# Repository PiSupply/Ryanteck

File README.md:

# Ryanteck

[Pi-Supply](https://uk.pi-supply.com) is one of the official distributors and manufacturers of [Ryanteck](https://ryanteck.uk) products including; RTK.GPIO, RTK Motor Controller board and RTK Traffic HAT for the Raspberry Pi. These product were designed by Ryan Walmsley at Ryanteck Ltd.

# Board overview

## RTK.GPIO

The RTK GPIO board allows you to connect the world of physical computing to you desktop PC or laptop. The RTK GPIO board emulates the original Raspberry Pi 28-pin GPIO header allowing you to program for the Raspberry Pi on your computer. The board is fully compatible with Windows, Mac OS and Linux and supports a range of programming languages such as Python.

The board connects to your computer using a micro USB cable , which also provides power to the board.

## RTK Motor Controller

The new and improved RTK-000-001-V3 / Motor Controller Board for Raspberry Pi is now pre-soldered and features a new and improved design breaking out the GPIO Pins to the side of the board.

The Ryanteck Raspberry Pi Motor Controller Board is a simple to use & budget friendly motor controller board for the Raspberry Pi which allows you to easily control 2 motors in both directions with some simple coding!

Once you receive the board, simply place it on the Raspberry Pi's GPIO header, screw in a power pack, add your motors and then start programming. We officially support Python at this point in time although you can use it with any language that allows you to control the GPIO pins including Scratch, C, Java, PHP, Bash, Node.JS etc.

## Traffic HAT

The Traffic HAT is designed for beginners to teach the basics or programming the real world with a traffic light sequence of LEDs. The HAT has 3 on-board LEDs (Red, Yellow, Green) with a push button and piezo buzzer.

The new Pi Supply branded Traffic HAT comes fully soldered and ready to go!

## Traffic pHAT

The Traffic pHAT is designed as a simple board to easily show the status of all the things! It is very much like the larger traffic HAT but with only 3 on-board LEDS (Red, Yellow, Green) and in a pHAT format. It comes with a 40 way GPIO header, so it perfect for any Raspberry Pi board with a 40 way connector.

The Traffic pHAT Comes fully assembled and ready to go!

## Where to buy

* [Pi Supply](https://uk.pi-supply.com)

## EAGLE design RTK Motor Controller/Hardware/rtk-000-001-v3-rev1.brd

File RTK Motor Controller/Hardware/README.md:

# RTK Motor Controller Board

The above image of the RTK Motor Controller Board PCB is used in the following descriptions to highlight some of the inputs and outputs and other useful hardware information of the board.

## Motor-1 Motor-2

These two screw terminals are used to connect two motors to the motor controller board. You can connect the wires from your motor to the terminals by un-screwing the screw and inserting the wire into the hole and the screw the terminal back down. The red wire should be inserted into the most left screw hole and the black next to it for a clockwise motor direction.

## VCC2

VCC2 screw terminal provides power to the motors and the motor controller chip. You can connect a power supply from 4.5V to 12V  with current up to 1A. The left terminal it the +V (Red wire) and the right terminal is GND (Black wire).

## GPIO Breakout Headers

There are two rows of 10 GPIO headers, which are breakout from the main 26-way Raspberry Pi GPIO header, JP2 and JP3 and also connected to the power input of VCC.

| JP3 | GPIO | JP2 | GPIO |
|-----|------|-----|------|
| 1   | VCC  | 1   | 5V      |
| 2   | 3V3  | 2   | 3V3     |
| 3   | GPIO 2| 3  | GPIO 14 |
| 4   | GPIO 3| 4  | GPIO 15 |
| 5   | GPIO 4| 5  | GPIO 24 |
| 6   | GPIO 10| 6 | GPIO 25 |
| 7   | GPIO 9| 7  | GPIO 8  |
| 8   | GPIO 11| 8 | GPIO 7  |
| 9   | GND | 9    | GND     |
| 10  | GND | 10   | GND     |

## SN75441ONE

The main active component is the SN75441ONE H-Bridge motor controller by TI.

| Pin Number | Label  | Connected to |
|------------|--------|--------------|
| 1          | 1,2 EN | VCC          |
| 2          | 1A     | GPIO 17      |
| 3          | 1Y     | Motor A 1    |
| 4          | GND_3  | GND          |
| 5          | GND_4  | GND          |
| 6          | 2Y     | Motor A 2    |
| 7          | 2A     | GPIO 18      |
| 8          | VCC2   | VCC/2        |
| 9          | 3,4 EN | VCC          |
| 10         | 3A     | GPIO 22      |
| 11         | 3Y     | Motor B 2    |
| 12         | GND    | GND          |
| 13         | GND_2  | GND          |
| 14         | 4Y     | Motor B 1    |
| 15         | 4A     | GPIO 23      |
| 16         | VCC 1  | VCC          |

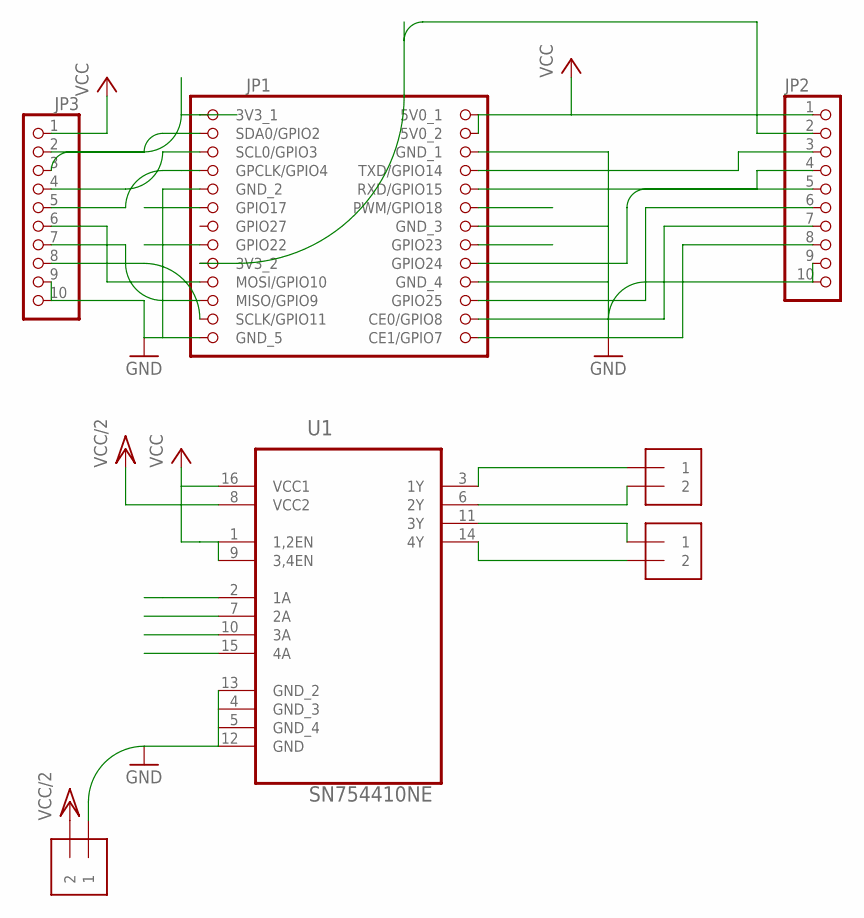
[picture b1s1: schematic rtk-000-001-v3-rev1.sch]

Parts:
JP1: RPIGPIOPINHD-2X13; 2X13
JP2, JP3: PINHD-1X10; 1X10
MOTOR-1, MOTOR-2: 1X2-3.5MM; 3.5MMTERM
U1: SN754410NE; DIP254P762X508-16
VCC2: 1X2-3.5MM; 3.5MMTERM

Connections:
17: JP1.11 (GPIO17), U1.2 (1A)
18: JP1.12 (PWM/GPIO18), U1.7 (2A)
22: JP1.15 (GPIO22), U1.10 (3A)
23: JP1.16 (GPIO23), U1.15 (4A)
GND: JP1.6 (GND_1), JP1.9 (GND_2), JP1.14 (GND_3), JP1.20 (GND_4), JP1.25 (GND_5), JP2.9, JP2.10, JP3.9, JP3.10, U1.4 (GND_3), U1.5 (GND_4), U1.12 (GND), U1.13 (GND_2), VCC2.1
GPIO24: JP1.18 (GPIO24), JP2.5
GPIO25: JP1.22 (GPIO25), JP2.6
unnamed: MOTOR-2.1, U1.11 (3Y)
unnamed: JP1.7 (GPCLK/GPIO4), JP3.5
unnamed: JP1.23 (SCLK/GPIO11), JP3.8
unnamed: MOTOR-2.2, U1.14 (4Y)
unnamed: MOTOR-1.2, U1.6 (2Y)
unnamed: MOTOR-1.1, U1.3 (1Y)
unnamed: JP1.19 (MOSI/GPIO10), JP3.6
unnamed: JP1.3 (SDA0/GPIO2), JP3.3
unnamed: JP1.5 (SCL0/GPIO3), JP3.4
unnamed: JP1.21 (MISO/GPIO9), JP3.7
unnamed: JP1.8 (TXD/GPIO14), JP2.3
unnamed: JP1.10 (RXD/GPIO15), JP2.4
unnamed: JP1.17 (3V3_2), JP2.2
unnamed: JP1.1 (3V3_1), JP3.2
unnamed: JP1.24 (CE0/GPIO8), JP2.7
unnamed: JP1.26 (CE1/GPIO7), JP2.8
VCC: JP1.2 (5V0_1), JP1.4 (5V0_2), JP2.1, JP3.1, U1.1 (1,2EN), U1.9 (3,4EN), U1.16 (VCC1)
VCC/2: U1.8 (VCC2), VCC2.2

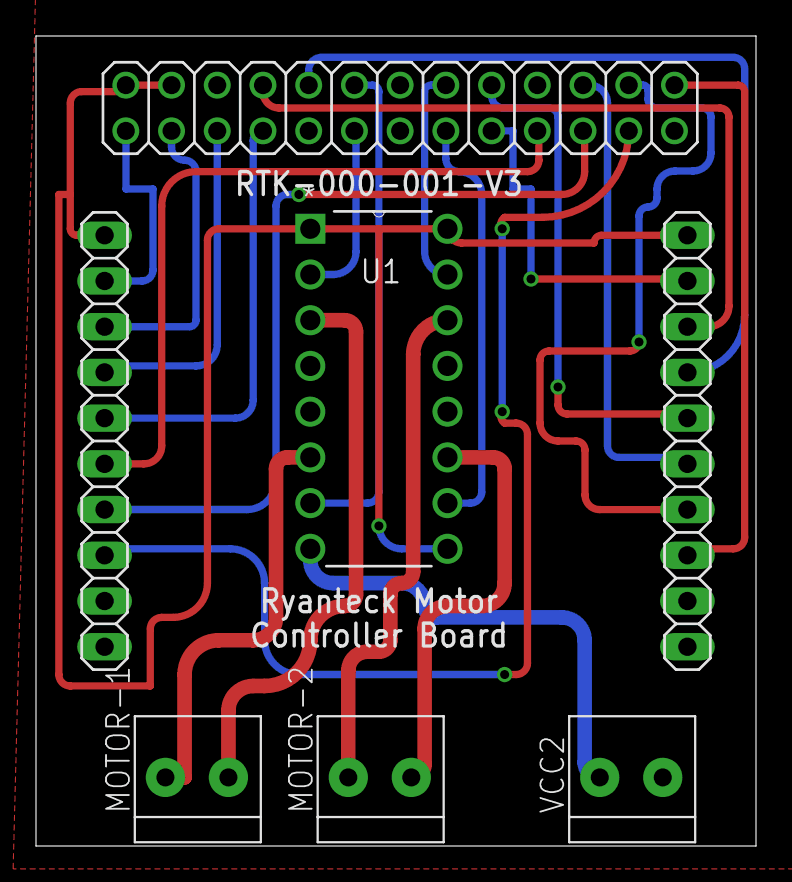
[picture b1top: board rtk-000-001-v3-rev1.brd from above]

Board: 2 copper layers, 40.0 x 45.0 mm, 7 parts (0 on the bottom side), 25 nets.

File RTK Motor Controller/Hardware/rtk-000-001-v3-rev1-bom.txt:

Partlist exported from C:/Users/Ryan/Documents/eagle/RTKMCBB/rtk-000-001-v3-rev1.sch at 24/07/2018 10:07

Qty Value      Device            Package           Parts                  Description                  MPN        OC_FARNELL OC_NEWARK PACKAGE SUPPLIER         
2              PINHD-1X10        1X10              JP2, JP3               PIN HEADER                                                                            
1              RPIGPIOPINHD-2X13 2X13              JP1                    RASPBERRY PI GPIO PIN HEADER                                                          
3   1X2-3.5MM  1X2-3.5MM         3.5MMTERM         MOTOR-1, MOTOR-2, VCC2 3.5mm Terminal block                                                                  
1   SN754410NE SN754410NE        DIP254P762X508-16 U1                     QUADRUPLE HALF-H DRIVERS     SN754410NE 1470411    08F8145   PDIP-16 Texas Instruments

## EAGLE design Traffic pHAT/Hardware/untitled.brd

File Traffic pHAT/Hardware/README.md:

# RTK Traffic pHAT

## Traffic pHAT Pinout

- Red LED - GPIO25 (pin 22)
- Yellow LED - GPIO24 (pin 18)
- Green LED - GPIO23 (pin 16)

## GPIO Pins Used

## EEPROM
The Traffic pHAT contains NO EEPROM, this was so it doesn't cause any conflicts with other HATs or pHATs.

## Schematic
The schematic can be found in both PDF format and as an Eagle CAD Schematic.

## Hardware
The hardware can be found as both Gerber format and EagleCAD BRD format. Along with BOM.

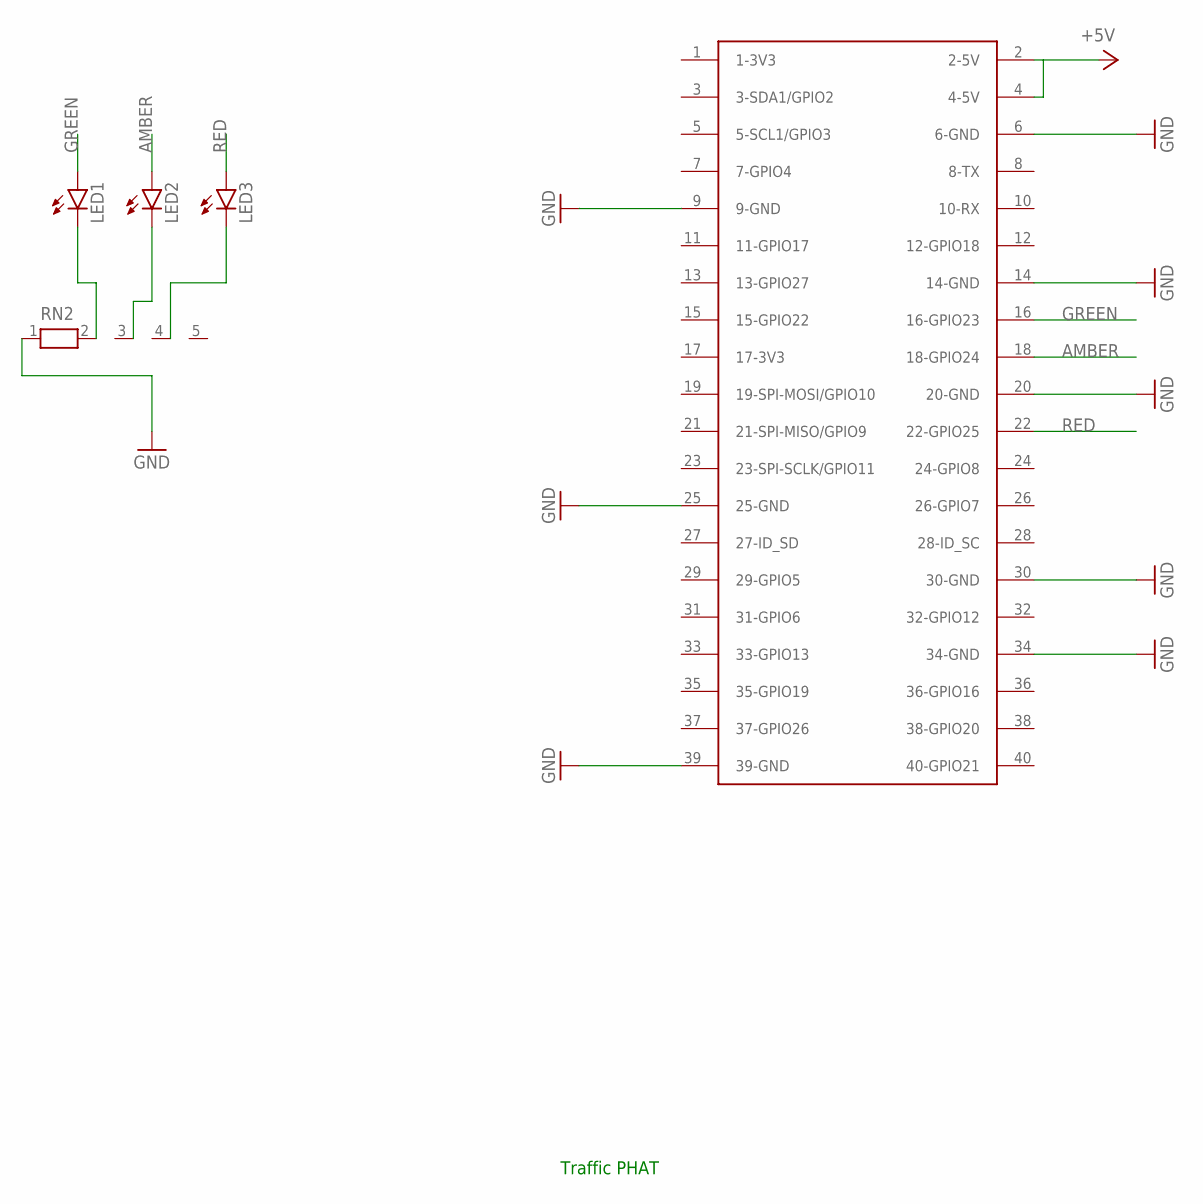
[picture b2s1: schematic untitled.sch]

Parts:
LED1, LED2, LED3: LED10MM
RN2: RN04; RN-5
U$1: RASPBERRY-PI+HEADERONLY; RASPBERRY-PI-PLUS-HEADERONLY

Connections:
+5V: U$1.2 (2-5V), U$1.4 (4-5V)
AMBER: LED2.A, U$1.18 (18-GPIO24)
GND: RN2.1, U$1.6 (6-GND), U$1.9 (9-GND), U$1.14 (14-GND), U$1.20 (20-GND), U$1.25 (25-GND), U$1.30 (30-GND), U$1.34 (34-GND), U$1.39 (39-GND)
GREEN: LED1.A, U$1.16 (16-GPIO23)
unnamed: LED1.K (C), RN2.2
unnamed: LED2.K (C), RN2.3
unnamed: LED3.K (C), RN2.4
RED: LED3.A, U$1.22 (22-GPIO25)

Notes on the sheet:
Traffic PHAT

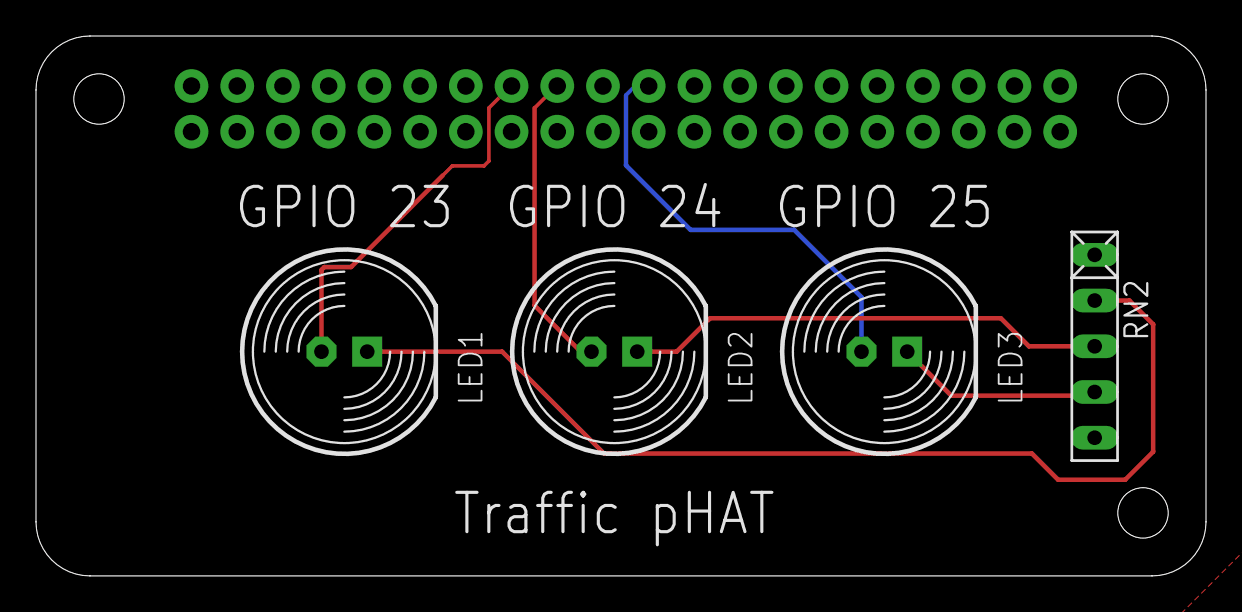
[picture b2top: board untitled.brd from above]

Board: 2 copper layers, 65.0 x 30.0 mm, 5 parts (0 on the bottom side), 8 nets.

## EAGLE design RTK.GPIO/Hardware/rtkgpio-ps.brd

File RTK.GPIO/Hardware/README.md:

# RTK GPIO

The above image of the RTK.GPIO PCB is used in the following descriptions to highlight some of the inputs and outputs and other useful hardware information of the board.

## GPIO header

The GPIO header replicates the current 40-way GPIO header of the Raspberry Pi with the following pinouts.

| Pin#   | Name | Name | Pin#   |
| ----   | ---- | ---- | ----   |
|   1    | 3.3V     | 5V     |   2    |
|   3    | GPIO02     | 5V     |   4    |
|   5    | GPIO03     | GND     |   6    |
|   7    | GPIO04     | GPIO14     |   8    |
|   9    | GND     | GPIO15     |   10   |
|   11   | GPIO17     | GPIO18     |   12   |
|   13   | GPIO27     | GND     |   14   |
|   15   | GPIO22     | GPIO23     |   16   |
|   17   | 3.3V     | GPIO024     |   18   |
|   19   | GPIO10     | GND     |   20   |
|   21   | GPIO09     | GPIO25     |   22   |
|   23   | GPIO11     | GPIO08     |   24   |
|   25   | GND     | GPIO07     |   26   |
|   27   | GPIO00     | GPIO01     |   28   |
|   29   | GPIO05     | GND     |   30   |
|   31   | GPIO06     | GPIO12     |   32   |
|   33   | GPIO13     | GND     |   34   |
|   35   | GPIO19     | GPIO16     |   36   |
|   37   | GPIO26     | GPIO20     |   38   |
|   39   | GND     | GPIO21     |   40   |

# I2C

The I2C header is a breakout header from the 40 way GPIO header, which allows you to directly connect I2C devices to the RTK.GPIO board and keep the header free.

1. 5V
2. SDA
3. SCL
4. GND

# PROG

The PROG header allows you to directly program the STM32F030 MCU using ST Link, ST Nucleo Programmer or ST Link Clone programmers.

1. SWDIO
2. SWCLK
3. Reset
4. GND

# UART
This UART header is another way in which you can connect the RTK.GPIO board to your computer using serial to USB communication. The UART header is connected to the CH340G serial to USB IC, which converts the signal and send it to the MCU.

1. 5V
2. RX
3. TX
4. GND

This is broken out so you can send commands direct to the RTk.GPIO over UART by interfacing with these pins.

# STM32F MCU

The main active microcontroller is a STM32F030C8T6 from ST microelectronics.

* Core ARM 32-bit Cortex M0 CPU 48MHz (Running at )
* 64 Kb Flash memory, 8 Kb SRAM
* 2.4-3.6V Operating voltage

# CH340G Serial to USB Convertor

The micro USB and UART connectors are connected to the serial chip interface, which converts USB to UART serial or vice versa when communicating between the MCU and your computer..

* Full speed USB 2.0 interface
* Supports common flow control signals RTS, DTR, DCD, RI, DSR and CTS
* Supports RS232, RS422 and RS485
* Uses the CH341 driver
* Supports both 5V and 3.3V operation

The CH340G on the RTk.GPIO uses UART Mode at 3v3. The RTk.GPIO uses a baudrate of 230400.

# Drivers

Links for divers:

## Windows: https://github.com/C0deGyver/CH340-Drivers-for-Windows
## Mac: https://github.com/adrianmihalko/ch340g-ch34g-ch34x-mac-os-x-driver

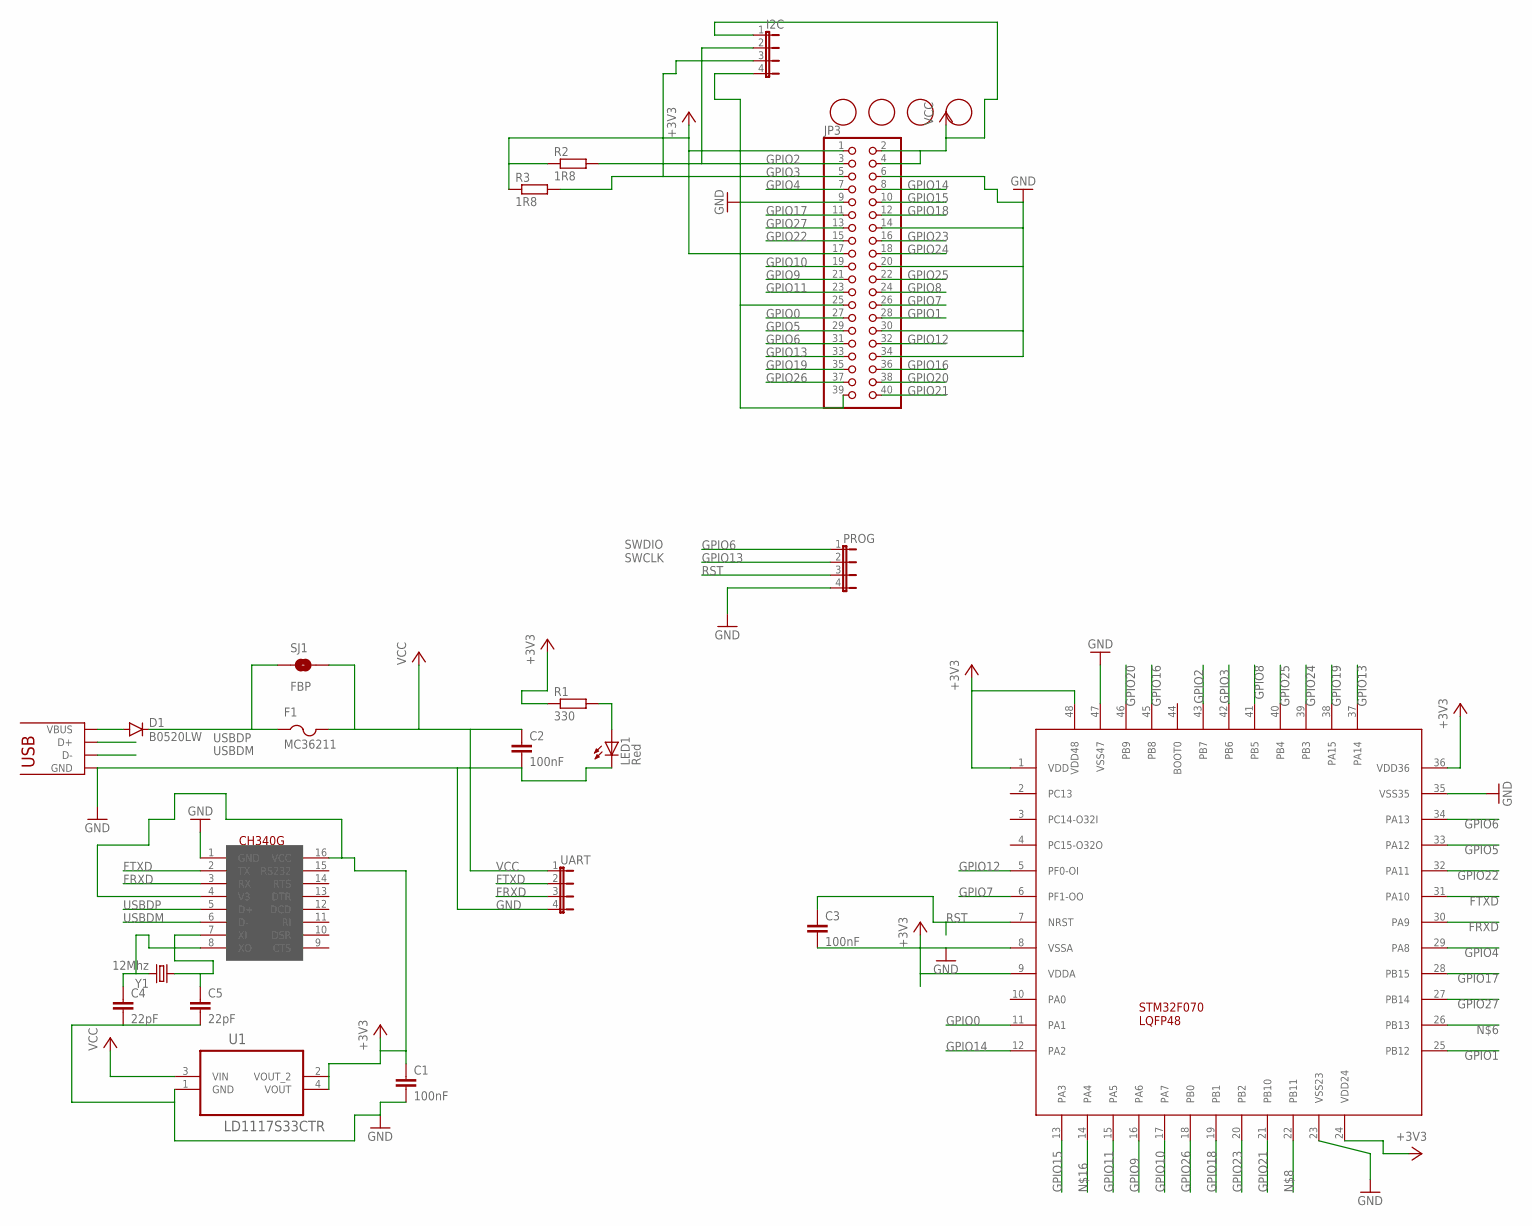
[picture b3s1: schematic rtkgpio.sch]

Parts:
C1, C2, C3: 100nF; C0402
C4, C5: 22pF; C0402
D1: B0520LW; SOD-123
F1: MC36211; R1206
I2C: JP4E; JP4
JP1: USB-MICROB
JP3: PINHD-2X20; 2X20
LED1: Red; SML1206
PROG: JP4E; JP4
R1: 330; R0402
R2, R3: 1R8; R0402
SJ1: FBP; SJ_2S-NO
U1: LD1117S33CTR; SOT230P700X180-4N
U$1: STM32F0X; LQFP-48
U$5, U$7, U$8, U$9: FIDUCIAL1MM; FIDUCIAL-1MM
U$6: CH340G; SOIC16
UART: JP4E; JP4
Y1: 12Mhz; SM49

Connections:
+3V3: C1.1, JP3.1, JP3.17, R1.1, R2.1, R3.1, U1.2 (VOUT_2), U1.4 (VOUT), U$1.1 (VDD), U$1.9 (VDDA), U$1.24 (VDD24), U$1.36 (VDD36), U$1.48 (VDD48), U$6.4 (V3), U$6.16 (VCC)
FRXD: U$1.30 (PA9), U$6.3 (RX), UART.3
FTXD: U$1.31 (PA10), U$6.2 (TX), UART.2
GND: C1.2, C2.2, C3.2, C4.2, C5.2, I2C.4, JP1.GND, JP1.MT1 (GND), JP1.MT2 (GND), JP1.P$1 (GND), JP1.P$2 (GND), JP1.P$3 (GND), JP1.P$4 (GND), JP3.6, JP3.9, JP3.14, JP3.20, JP3.25, JP3.30, JP3.34, JP3.39, LED1.C, PROG.4, U1.1 (GND), U$1.8 (VSSA), U$1.23 (VSS23), U$1.35 (VSS35), U$1.47 (VSS47), U$6.1 (GND), UART.4
GPIO0: JP3.27, U$1.11 (PA1)
GPIO1: JP3.28, U$1.25 (PB12)
GPIO2: I2C.2, JP3.3, R2.2, U$1.43 (PB7)
GPIO3: I2C.3, JP3.5, R3.2, U$1.42 (PB6)
GPIO4: JP3.7, U$1.29 (PA8)
GPIO5: JP3.29, U$1.33 (PA12)
GPIO6: JP3.31, PROG.1, U$1.34 (PA13)
GPIO7: JP3.26, U$1.6 (PF1-OO)
GPIO8: JP3.24, U$1.41 (PB5)
GPIO9: JP3.21, U$1.16 (PA6)
GPIO10: JP3.19, U$1.17 (PA7)
GPIO11: JP3.23, U$1.15 (PA5)
GPIO12: JP3.32, U$1.5 (PF0-OI)
GPIO13: JP3.33, PROG.2, U$1.37 (PA14)
GPIO14: JP3.8, U$1.12 (PA2)
GPIO15: JP3.10, U$1.13 (PA3)
GPIO16: JP3.36, U$1.45 (PB8)
GPIO17: JP3.11, U$1.28 (PB15)
GPIO18: JP3.12, U$1.19 (PB1)
GPIO19: JP3.35, U$1.38 (PA15)
GPIO20: JP3.38, U$1.46 (PB9)
GPIO21: JP3.40, U$1.21 (PB10)
GPIO22: JP3.15, U$1.32 (PA11)
GPIO23: JP3.16, U$1.20 (PB2)
GPIO24: JP3.18, U$1.39 (PB3)
GPIO25: JP3.22, U$1.40 (PB4)
GPIO26: JP3.37, U$1.18 (PB0)
GPIO27: JP3.13, U$1.27 (PB14)
unnamed: C5.1, U$6.7 (XI), Y1.1
unnamed: C4.1, U$6.8 (XO), Y1.2
unnamed: LED1.A, R1.2
unnamed: D1.C, F1.1, SJ1.1
unnamed: D1.A, JP1.VBUS
RST: C3.1, PROG.3, U$1.7 (NRST)
USBDM: JP1.D-, U$6.6 (D-)
USBDP: JP1.D+, U$6.5 (D+)
VCC: C2.1, F1.2, I2C.1, JP3.2, JP3.4, SJ1.2, U1.3 (VIN), UART.1

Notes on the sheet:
SWDIO SWCLK

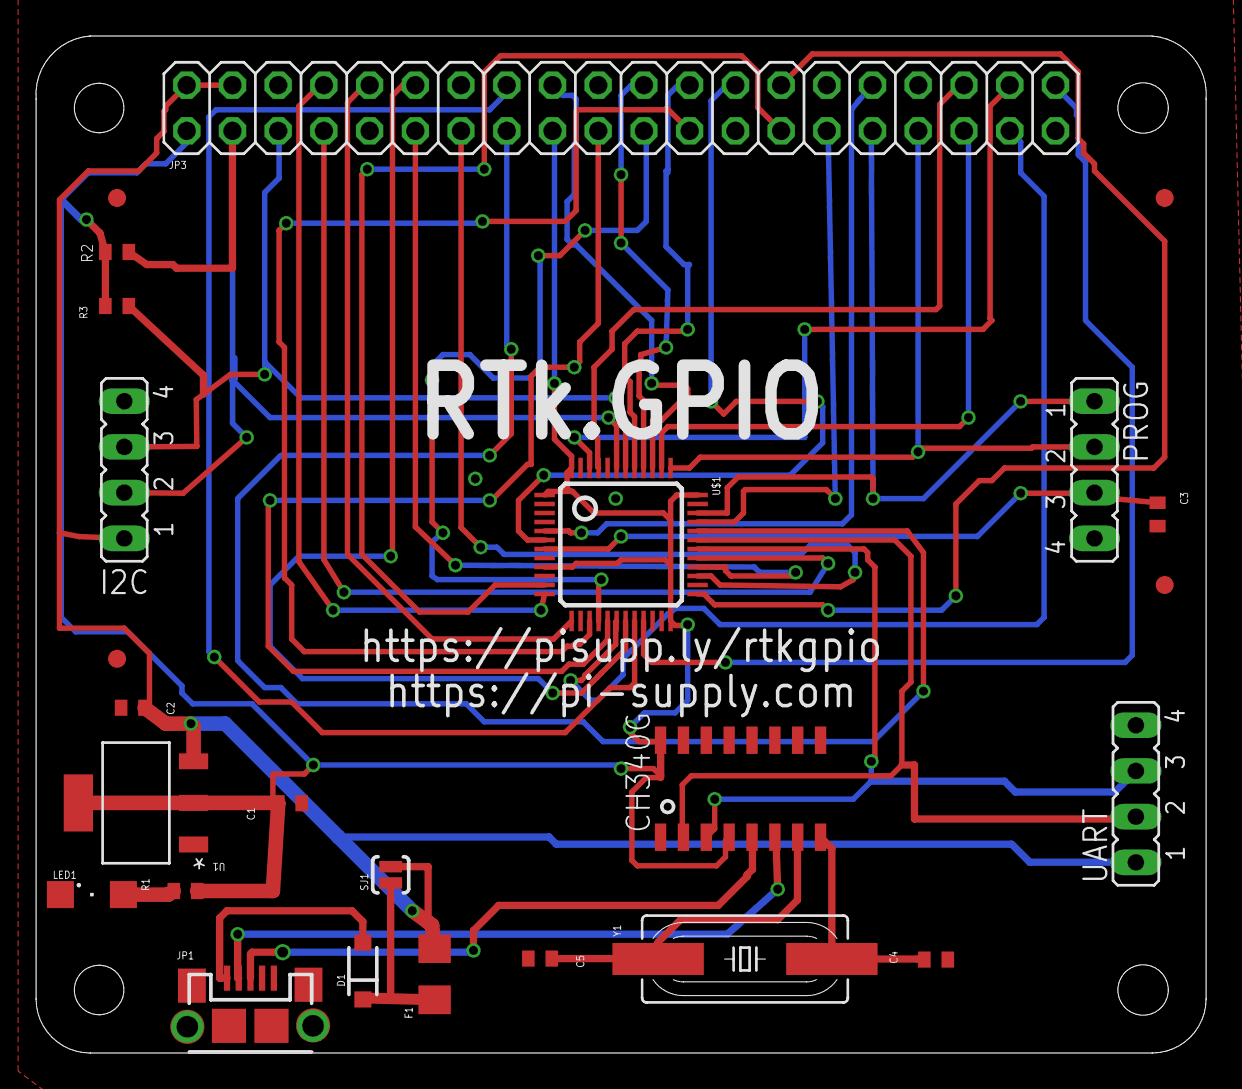
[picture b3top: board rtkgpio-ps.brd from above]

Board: 2 copper layers, 65.0 x 56.5 mm, 26 parts (1 on the bottom side), 41 nets.

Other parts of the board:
U$2: TONNE_10.00

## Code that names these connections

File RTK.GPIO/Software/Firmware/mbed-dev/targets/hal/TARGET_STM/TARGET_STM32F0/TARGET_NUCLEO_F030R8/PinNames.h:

/* mbed Microcontroller Library
 *******************************************************************************
 * Copyright (c) 2014, STMicroelectronics
 * All rights reserved.
 *
 * Redistribution and use in source and binary forms, with or without
 * modification, are permitted provided that the following conditions are met:
 *
 * 1. Redistributions of source code must retain the above copyright notice,
 *    this list of conditions and the following disclaimer.
 * 2. Redistributions in binary form must reproduce the above copyright notice,
 *    this list of conditions and the following disclaimer in the documentation
 *    and/or other materials provided with the distribution.
 * 3. Neither the name of STMicroelectronics nor the names of its contributors
 *    may be used to endorse or promote products derived from this software
 *    without specific prior written permission.
 *
 * THIS SOFTWARE IS PROVIDED BY THE COPYRIGHT HOLDERS AND CONTRIBUTORS "AS IS"
 * AND ANY EXPRESS OR IMPLIED WARRANTIES, INCLUDING, BUT NOT LIMITED TO, THE
 * IMPLIED WARRANTIES OF MERCHANTABILITY AND FITNESS FOR A PARTICULAR PURPOSE ARE
 * DISCLAIMED. IN NO EVENT SHALL THE COPYRIGHT HOLDER OR CONTRIBUTORS BE LIABLE
 * FOR ANY DIRECT, INDIRECT, INCIDENTAL, SPECIAL, EXEMPLARY, OR CONSEQUENTIAL
 * DAMAGES (INCLUDING, BUT NOT LIMITED TO, PROCUREMENT OF SUBSTITUTE GOODS OR
 * SERVICES; LOSS OF USE, DATA, OR PROFITS; OR BUSINESS INTERRUPTION) HOWEVER
 * CAUSED AND ON ANY THEORY OF LIABILITY, WHETHER IN CONTRACT, STRICT LIABILITY,
 * OR TORT (INCLUDING NEGLIGENCE OR OTHERWISE) ARISING IN ANY WAY OUT OF THE USE
 * OF THIS SOFTWARE, EVEN IF ADVISED OF THE POSSIBILITY OF SUCH DAMAGE.
 *******************************************************************************
 */
#ifndef MBED_PINNAMES_H
#define MBED_PINNAMES_H

#include "cmsis.h"

#ifdef __cplusplus
extern "C" {
#endif

// See stm32f0xx_hal_gpio.h and stm32f0xx_hal_gpio_ex.h for values of MODE, PUPD and AFNUM
#define STM_PIN_DATA(MODE, PUPD, AFNUM)  ((int)(((AFNUM) << 7) | ((PUPD) << 4) | ((MODE) << 0)))
#define STM_PIN_MODE(X)   (((X) >> 0) & 0x0F)
#define STM_PIN_PUPD(X)   (((X) >> 4) & 0x07)
#define STM_PIN_AFNUM(X)  (((X) >> 7) & 0x0F)
#define STM_MODE_INPUT              (0)
#define STM_MODE_OUTPUT_PP          (1)
#define STM_MODE_OUTPUT_OD          (2)
#define STM_MODE_AF_PP              (3)
#define STM_MODE_AF_OD              (4)
#define STM_MODE_ANALOG             (5)
#define STM_MODE_IT_RISING          (6)
#define STM_MODE_IT_FALLING         (7)
#define STM_MODE_IT_RISING_FALLING  (8)
#define STM_MODE_EVT_RISING         (9)
#define STM_MODE_EVT_FALLING        (10)
#define STM_MODE_EVT_RISING_FALLING (11)
#define STM_MODE_IT_EVT_RESET       (12)

// High nibble = port number (0=A, 1=B, 2=C, 3=D, 4=E, 5=F, 6=G, 7=H)
// Low nibble  = pin number
#define STM_PORT(X) (((uint32_t)(X) >> 4) & 0xF)
#define STM_PIN(X)  ((uint32_t)(X) & 0xF)

typedef enum {
    PIN_INPUT,
    PIN_OUTPUT
} PinDirection;

typedef enum {
    PA_0  = 0x00,
    PA_1  = 0x01,
    PA_2  = 0x02,
    PA_3  = 0x03,
    PA_4  = 0x04,
    PA_5  = 0x05,
    PA_6  = 0x06,
    PA_7  = 0x07,
    PA_8  = 0x08,
    PA_9  = 0x09,
    PA_10 = 0x0A,
    PA_11 = 0x0B,
    PA_12 = 0x0C,
    PA_13 = 0x0D,
    PA_14 = 0x0E,
    PA_15 = 0x0F,

    PB_0  = 0x10,
    PB_1  = 0x11,
    PB_2  = 0x12,
    PB_3  = 0x13,
    PB_4  = 0x14,
    PB_5  = 0x15,
    PB_6  = 0x16,
    PB_7  = 0x17,
    PB_8  = 0x18,
    PB_9  = 0x19,
    PB_10 = 0x1A,
    PB_11 = 0x1B,
    PB_12 = 0x1C,
    PB_13 = 0x1D,
    PB_14 = 0x1E,
    PB_15 = 0x1F,

    PC_0  = 0x20,
    PC_1  = 0x21,
    PC_2  = 0x22,
    PC_3  = 0x23,
    PC_4  = 0x24,
    PC_5  = 0x25,
    PC_6  = 0x26,
    PC_7  = 0x27,
    PC_8  = 0x28,
    PC_9  = 0x29,
    PC_10 = 0x2A,
    PC_11 = 0x2B,
    PC_12 = 0x2C,
    PC_13 = 0x2D,
    PC_14 = 0x2E,
    PC_15 = 0x2F,

    PD_2  = 0x32,

    PF_0  = 0x50,
    PF_1  = 0x51,
    PF_4  = 0x54,
    PF_5  = 0x55,
    PF_6  = 0x56,
    PF_7  = 0x57,


    // RTk.GPIO Connector Namings
    GPIO0          = PA_1,
    GPIO1          = PB_12,
    GPIO2          = PB_7,
    GPIO3          = PB_6,
    GPIO4          = PA_8,
    GPIO5          = PA_12,
    GPIO6          = PA_13,
    GPIO7          = PF_1,
    GPIO8          = PB_5,
    GPIO9          = PA_6,
    GPIO10          = PA_7,
    GPIO11          = PA_5,
    GPIO12          = PF_0,
    GPIO13          = PA_14,
    GPIO14          = PA_2,
    GPIO15          = PA_3,
    GPIO16          = PB_8,
    GPIO17          = PB_15,
    GPIO18         = PB_1,
    GPIO19         = PA_15,
    GPIO20         = PB_9,
    GPIO21         = PB_10,
    GPIO22         = PA_11,
    GPIO23         = PB_2,
    GPIO24         = PB_3,
    GPIO25         = PB_4,
    GPIO26         = PB_0,
    GPIO27         = PB_14,

    // Generic signals namings
    LED1        = PA_5,
    LED2        = PA_5,
    LED3        = PA_5,
    LED4        = PA_5,
    USER_BUTTON = PC_13,
    SERIAL_TX   = PA_9,
    SERIAL_RX   = PA_10,
    USBTX       = PA_2,
    USBRX       = PA_3,
    I2C_SCL     = PB_8,
    I2C_SDA     = PB_9,
    SPI_MOSI    = PA_7,
    SPI_MISO    = PA_6,
    SPI_SCK     = PA_5,
    SPI_CS      = PB_6,
    PWM_OUT     = PC_7,

    // Not connected
    NC = (int)0xFFFFFFFF
} PinName;

typedef enum {
    PullNone  = 0,
    PullUp    = 1,
    PullDown  = 2,
    OpenDrain = 3,
    PullDefault = PullNone
} PinMode;

#ifdef __cplusplus
}
#endif

#endif

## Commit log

2018-06-25 Documentation
    RyanTeck Documentation and project code
    RTK.GPIO
    - Hardware
    - Software
    RTK Motor Controller
    - Hardware
2018-06-25 Quickstart Guide
    A quickstart guide for using the RTk.GPIO board
2018-06-27 Getting Started Guide
2018-06-27 Motor Controller Guide
2018-09-03 Added pinout tables for motor controller
2018-10-28 Update README
    The ProMicro.inf file is not included in the Rtk.GPIO repository, and on investigation is no longer in the reference Sparkfun one either. The folder referenced in the Anyio repository is no longer co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
2018-10-28 Removed secondary undeeded readme
2018-10-28 Some spelling fixes and added in the fact USB cable is now included.
2018-10-30 Formatting improvements, copyright updates
2018-10-30 Changed motors to use variables, this way it should be easier if they wire the motor round the wrong way
2018-10-30 Markdown fixes for github
2018-10-30 More formatting improvements
2018-10-30 Some bits added to the readme of more specification, removed a test file which isn't intended to be distributed.
2019-02-10 I have added a "fake" implementation of PWM using sleep. In the PWM class there is a simple DutyCycle calculator to make controlling PWM servos easier.
    I changed the Software/examples/testPWM.py file to use the new PWM fuinctionality.
    I created an example LED test file as there was no output test file currently.
    I added a drivers section in Hardware/README.md as I did not realize installing a driver was nessary (in Windows 7 at least)
2019-10-31 Documentation
    CE/FCC/EMC docs
2020-02-07 add banner
2020-06-24 Documentation
    - Added schematic diagram
    - Board pinout
2020-06-24 Documentation
    - Updated image links
    - Corrected formating
2020-06-24 Start work on trademarks and organising repository correctly.
2020-06-24 Add licenses
2020-06-24 Add trademark sections
2020-06-24 Worksheets
2020-06-24 Add more hardawre info.
2020-06-24 Remaining files
2020-06-24 MD formatting fixes
2020-06-24 Change logo directory
2020-06-24 Update description
2020-07-05 Remove unnecessary parentheses
2020-09-11 Update README.md
    This space keeps bugging me
2020-09-14 Initial commits for pHat
2020-09-14 OSHWA all the things
2020-09-14 OSHW Certification
    Traffic HAT OSHW
2020-09-14 Update README.md
    Resized image
2020-09-14 Tidy images up into the acutal repo to comply with oshw stuff
2020-09-14 Fix images so they're uploaded properly rather than as issues.
2020-09-14 More image fixes
2020-09-14 Update blurb
2020-09-14 think we include the micro usb now
2020-09-14 New images
2020-09-14 Remove scratch support due to changes
2020-09-14 Scratch never developed, don't think I once said java so removed them to be corrected.
2020-09-14 Spelling mistake
2020-09-14 Another spelling mistake
2020-09-15 Open Source GPIO Board
2020-09-15 IMAGE
2020-09-15 pngy
2020-09-15 Fix confusion
2020-09-15 Remove java
2020-09-15 Add MCB
2020-09-15 Add the gerby gerbers
2020-09-19 Add licenses in
2020-09-19 Licensey
2020-09-20 Add logos
2020-09-20 RTk.GPIO
2020-09-20 Traffic pHAT
2020-09-20 Width
2020-09-20 Width 2
2020-09-20 Width?
2020-09-20 Back with width
2020-09-20 Resized
2020-09-20 Trafficphat
2020-09-20 Add new image
2020-09-21 Revert back
2020-09-21 Add back in cropped image
2020-09-21 re-crop
2020-09-21 Rename
2020-10-01 Should fix issue #7
2020-10-01 Remove official scratch support as Scratch GPIO has changed since this.
2020-10-01 Wiring Pi Discontinued Notice
2020-10-01 Node JS has changed significantly since this.
2020-10-01 Update incorrect voltage.
2020-10-01 Update image to match
2020-10-01 Fix formatting
2020-10-01 Neaten Up
2020-10-01 Traffic pHAT Demo
2020-10-01 Renamed
2020-10-01 Fix description issue
2020-12-28 Create CH341SER.EXE
    Add drivers

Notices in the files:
parts and their libraries:
pimoroni2: Licensing: CC v3.0 Share-Alike You are welcome to use this library for commercial purposes.
SparkFun-DiscreteSemi: Licensing: Creative Commons ShareAlike 4.0 International - https://creativecommons.org/licenses/by-sa/4.0
